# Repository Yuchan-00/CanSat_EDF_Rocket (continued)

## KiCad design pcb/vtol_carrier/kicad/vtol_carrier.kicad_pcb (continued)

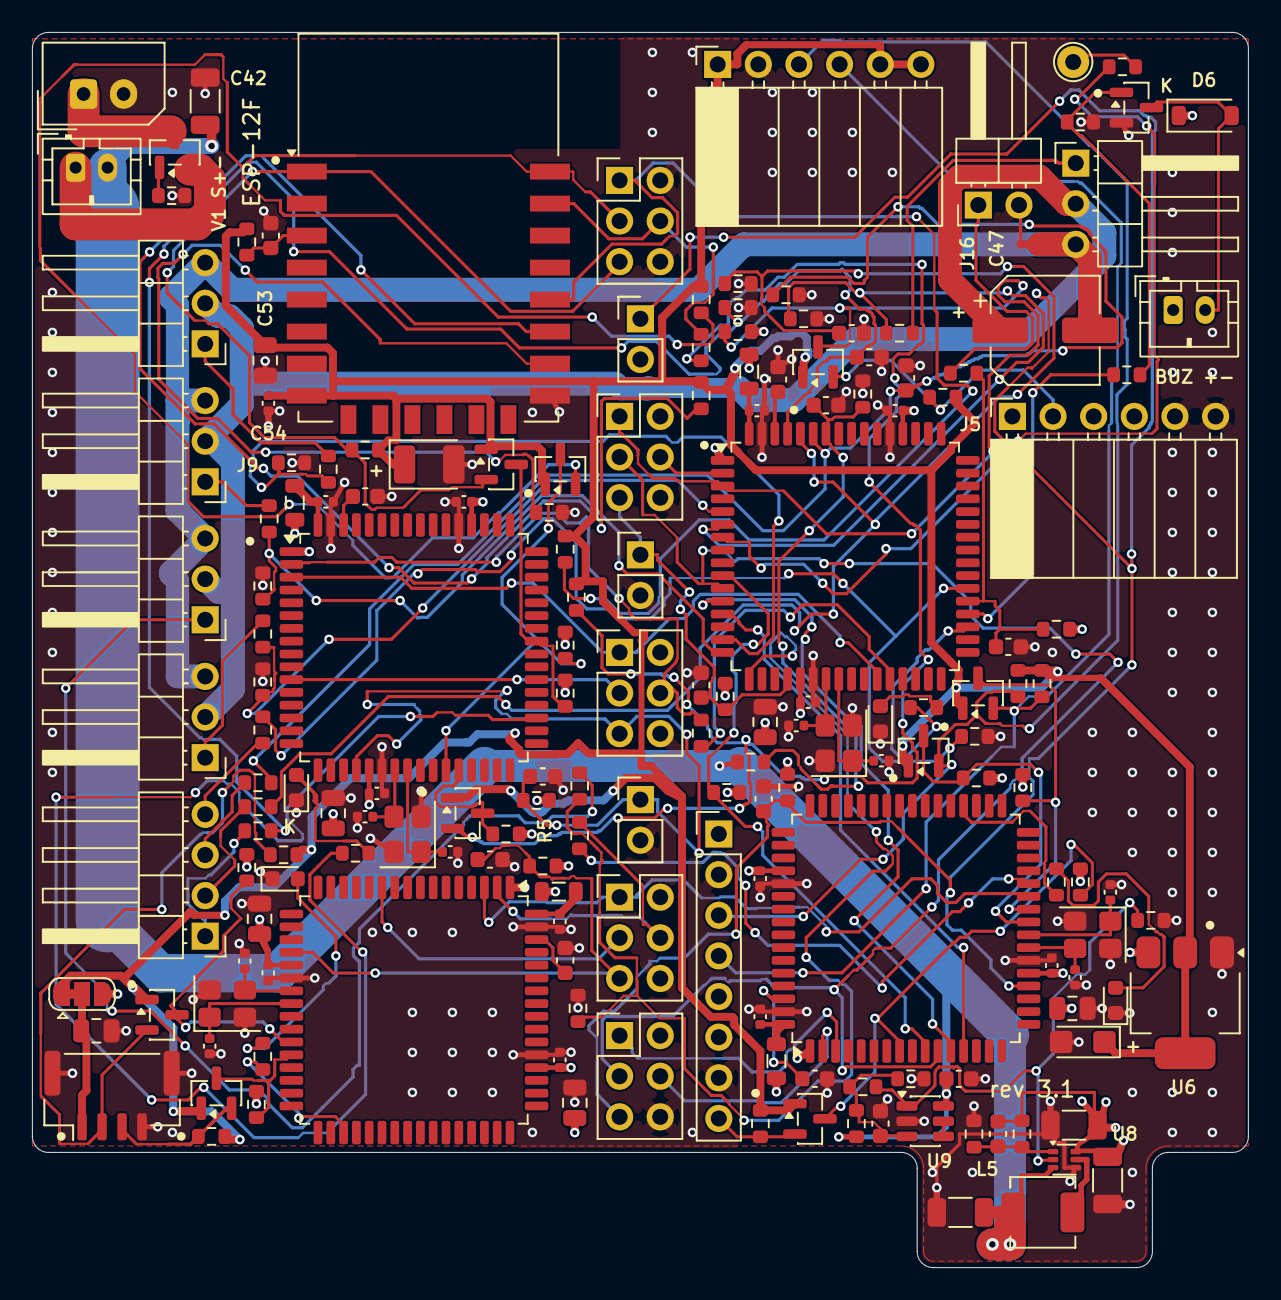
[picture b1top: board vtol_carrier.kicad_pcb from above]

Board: 4 copper layers, 76.0 x 77.2 mm, 176 parts (0 on the bottom side), 107 nets.

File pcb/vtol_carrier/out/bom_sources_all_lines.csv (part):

line,value,fitted refs,qty fitted,DNP refs,footprint,source,part number,MPN / name,JLC type,assembly,URL fetched,fetch date,stock at fetch
c100n0402,100n,C1 C2 C4 C9 C10 C12 C17 C18 C20 C25 C26 C28 C54,13,,Capacitor_SMD:C_0402_1005Metric,JLCPCB/LCSC,C1525,CL05B104KO5NNNC,Basic,JLC SMT assembly,https://jlcpcb.com/partdetail/C1525 https://cart.jlcpcb.com/shoppingCart/smtGood/getComponentDet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 https://www.lcsc.com/product-detail/multilayer-ceramic-capac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,2026-11-05,33539946
c10u0805,10u,C3 C11 C19 C27 C44 C53 C56,7,,Capacitor_SMD:C_0805_2012Metric,JLCPCB/LCSC,C15850,CL21A106KAYNNNE,Basic,JLC SMT assembly,https://jlcpcb.com/partdetail/C15850 https://cart.jlcpcb.com/shoppingCart/smtGood/getComponentDet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 https://www.lcsc.com/product-detail/multilayer-ceramic-capac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,2026-11-05,7647363
c100n0603,100n,C5 C8 C13 C16 C21 C24 C29 C32 C46 C48 C49 C50 C51 C55,14,,Capacitor_SMD:C_0603_1608Metric,JLCPCB/LCSC,C14663,CC0603KRX7R9BB104,Basic,JLC SMT assembly,https://jlcpcb.com/partdetail/C14663 https://cart.jlcpcb.com/shoppingCart/smtGood/getComponentDet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 https://www.lcsc.com/product-detail/multilayer-ceramic-capac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,2026-11-05,37483003
c27p0402,27p,C6 C7 C14 C15 C22 C23 C30 C31,8,,Capacitor_SMD:C_0402_1005Metric,JLCPCB/LCSC,C1557,0402CG270J500NT,Extended,JLC SMT assembly,https://jlcpcb.com/partdetail/C1557 https://cart.jlcpcb.com/shoppingCart/smtGood/getComponentDet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 https://www.lcsc.com/product-detail/multilayer-ceramic-capac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,2026-11-05,292832
c22u1206,22u 10V,C41 C42 C43,3,,Capacitor_SMD:C_1206_3216Metric,JLCPCB/LCSC,C12891,CL31A226KAHNNNE,Basic,JLC SMT assembly,https://jlcpcb.com/partdetail/C12891 https://cart.jlcpcb.com/shoppingCart/smtGood/getComponentDet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 https://www.lcsc.com/product-detail/multilayer-ceramic-capac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,2026-11-05,1628107
tant22u,22u 10V tantalum,C45,1,,Capacitor_Tantalum_SMD:CP_EIA-3216-18_Kemet-A,JLCPCB/LCSC,C7183,TAJA226M010RNJ,Extended,JLC SMT assembly,https://jlcpcb.com/partdetail/C7183 https://cart.jlcpcb.com/shoppingCart/smtGood/getComponentDet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 https://www.lcsc.com/product-detail/tantalum-capacitors_kyoc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,2026-11-05,2307
elec220u,220u 10V,C47,1,,Capacitor_SMD:CP_Elec_6.3x5.4,JLCPCB/LCSC,C2833309,RVT220UF10V67RV0037,Extended,JLC SMT assembly,https://jlcpcb.com/partdetail/C2833309 https://cart.jlcpcb.com/shoppingCart/smtGood/getComponentDet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 https://www.lcsc.com/product-detail/aluminum-electrolytic-ca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,2026-11-05,205404
tant100u,100u 10V tantalum,C52,1,,Capacitor_Tantalum_SMD:CP_EIA-3528-21_Kemet-B,JLCPCB/LCSC,C7196,TAJB107M010RNJ,Extended,JLC SMT assembly,https://jlcpcb.com/partdetail/C7196 https://cart.jlcpcb.com/shoppingCart/smtGood/getComponentDet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 https://www.lcsc.com/product-detail/tantalum-capacitors_kyoc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,2026-11-05,105178
led,LED 0603 (colour A),D1 D2 D3 D4,4,,LED_SMD:LED_0603_1608Metric,JLCPCB/LCSC,C2286,KT-0603R,Basic,JLC SMT assembly,https://jlcpcb.com/partdetail/C2286 https://cart.jlcpcb.com/shoppingCart/smtGood/getComponentDet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 https://www.lcsc.com/product-detail/led-indication-discrete_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,2026-11-05,6721348
schottky,SS14 / B5819W class Schottky,D6,1,,Diode_SMD:D_SOD-123,JLCPCB/LCSC,C8598,B5819W SL,Basic,JLC SMT assembly,https://jlcpcb.com/partdetail/C8598 https://cart.jlcpcb.com/shoppingCart/smtGood/getComponentDet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 https://www.lcsc.com/product-detail/schottky-diodes_jiangsu-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,2026-11-05,811852
gy521,1x8 2.54 mm (GY-521 soldered flat on straight pins),J1,1,,Connector_PinHeader_2.54mm:PinHeader_1x08_P2.54mm_Vertical,devicemart,no=1247052,MPU-6050 6축 자이로 가속도 센서 모듈 GY-521 [SZH-EK007],,hand-solder (devicemart module),https://www.devicemart.co.kr/goods/view?no=1247052 https://www.devicemart.co.kr/goods/search_sse_stream?search_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,2026-11-05,0
sock1x6ra,1x6 2.54 mm right-angle socket (module lies flat),J2 J5,2,,Connector_PinSocket_2.54mm:PinSocket_1x06_P2.54mm_Horizontal,JLCPCB/LCSC,C55629861,SH-PM254R-1x6P-H85,Extended,hand-solder (THT; JLC THT assembly optional),https://jlcpcb.com/partdetail/C55629861 https://cart.jlcpcb.com/shoppingCart/smtGood/getComponentDet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 ,2026-11-05,985
hdr2x3,2x3 2.54 mm vertical: ESP-12E programming header (3.3 V logic ONLY),,0,J3 J19 J20 J21 J22,Connector_PinHeader_2.54mm:PinHeader_2x03_P2.54mm_Vertical,JLCPCB/LCSC,C65114,2.54-2*3PPin,Extended,hand-solder (THT; JLC THT assembly optional),https://jlcpcb.com/partdetail/C65114 https://cart.jlcpcb.com/shoppingCart/smtGood/getComponentDet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 https://www.lcsc.com/product-detail/pin-headers_boomele-boom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,2026-11-05,41728
boost,"1x5 2.54 mm: Pololu S9V11F5S6CMA 5 V step-up/step-down module (VOUT, GND, VIN, EN, PG)",J6,1,,Connector_PinHeader_2.54mm:PinHeader_1x05_P2.54mm_Vertical,devicemart,no=15855364,5V Step-Up/Step-Down Voltage Regulator w/ Adjustable Low-Voltage Cutoff S9V11F5S6CMA #2870,,hand-solder (devicemart module),https://www.devicemart.co.kr/goods/view?no=15855364 https://www.devicemart.co.kr/goods/search_sse_stream?search_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,2026-11-05,100
gh4,JST-GH 1.25 mm 4-pin vertical (top entry),J7,1,,Connector_JST:JST_GH_BM04B-GHS-TBT_1x04-1MP_P1.25mm_Vertical,JLCPCB/LCSC,C161692,BM04B-GHS-TBT(LF)(SN),Extended,JLC SMT assembly,https://jlcpcb.com/partdetail/C161692 https://cart.jlcpcb.com/shoppingCart/smtGood/getComponentDet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 https://www.lcsc.com/product-detail/wire-to-board-connector_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,2026-11-05,23326
hdr1x3ra,"1x3 2.54 mm right-angle header (S, +, -)",J8 J9 J10 J11 J12,5,,Connector_PinHeader_2.54mm:PinHeader_1x03_P2.54mm_Horizontal,JLCPCB/LCSC,C55629817,SH-PZ254R-1x3P,Extended,hand-solder (THT; JLC THT assembly optional),https://jlcpcb.com/partdetail/C55629817 https://cart.jlcpcb.com/shoppingCart/smtGood/getComponentDet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 ,2026-11-05,2000
spox2,"Molex SPOX 5267-02A 2.50 mm 2-pin vertical (mates the pack's 5264-type housing, A)",J14,1,,Connector_Molex:Molex_SPOX_5267-02A_1x02_P2.50mm_Vertical,JLCPCB/LCSC,C5364642,22035025,Extended,hand-solder (THT; JLC THT assembly optional),https://jlcpcb.com/partdetail/C5364642 https://cart.jlcpcb.com/shoppingCart/smtGood/getComponentDet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 https://www.lcsc.com/product-detail/wire-to-board-connector_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,2026-11-05,454
ph2,JST-PH 2.0 2-pin vertical: lead to an external logic power switch,J15 J17,2,,Connector_JST:JST_PH_B2B-PH-K_1x02_P2.00mm_Vertical,JLCPCB/LCSC,C131337,B2B-PH-K-S(LF)(SN),Extended,hand-solder (THT; JLC THT assembly optional),https://jlcpcb.com/partdetail/C131337 https://cart.jlcpcb.com/shoppingCart/smtGood/getComponentDet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 https://www.lcsc.com/product-detail/wire-to-board-connector_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,2026-11-05,214800
hdr1x2ra,1x2 right-angle header,J16,1,,Connector_PinHeader_2.54mm:PinHeader_1x02_P2.54mm_Horizontal,JLCPCB/LCSC,C55629816,SH-PZ254R-1x2P,Extended,hand-solder (THT; JLC THT assembly optional),https://jlcpcb.com/partdetail/C55629816 https://cart.jlcpcb.com/shoppingCart/smtGood/getComponentDet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 ,2026-11-05,1750
hdr1x4ra,1x4 right-angle header,J18,1,,Connector_PinHeader_2.54mm:PinHeader_1x04_P2.54mm_Horizontal,JLCPCB/LCSC,C55629818,SH-PZ254R-1x4P,Extended,hand-solder (THT; JLC THT assembly optional),https://jlcpcb.com/partdetail/C55629818 https://cart.jlcpcb.com/shoppingCart/smtGood/getComponentDet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 ,2026-11-05,1898
hdr1x2v,2-pin header + shunt,,0,J24 J25 J26,Connector_PinHeader_2.54mm:PinHeader_1x02_P2.54mm_Vertical,JLCPCB/LCSC,C55629809,SH-PZ254V-1x2P,Extended,hand-solder (THT; JLC THT assembly optional),https://jlcpcb.com/partdetail/C55629809 https://cart.jlcpcb.com/shoppingCart/smtGood/getComponentDet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 ,2026-11-05,1662
ind10u,10uH,L1 L2 L3 L4,4,,Inductor_SMD:L_0805_2012Metric,JLCPCB/LCSC,C1046,SDFL2012S100KTF,Basic,JLC SMT assembly,https://jlcpcb.com/partdetail/C1046 https://cart.jlcpcb.com/shoppingCart/smtGood/getComponentDet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 https://www.lcsc.com/product-detail/inductors-smd_sunlord-sd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,2026-11-05,211090
bss138,BSS138,Q1 Q2 Q4 Q5 Q6 Q7 Q8 Q11,8,Q3,Package_TO_SOT_SMD:SOT-23,JLCPCB/LCSC,C40912,BSS138-7-F,Extended,JLC SMT assembly,https://jlcpcb.com/partdetail/C40912 https://cart.jlcpcb.com/shoppingCart/smtGood/getComponentDet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 https://www.lcsc.com/product-detail/mosfets_diodes-incorpora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,2026-11-05,409427
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
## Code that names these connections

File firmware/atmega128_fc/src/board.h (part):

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 * Every assignment below comes from params.json - FCU: flight_computer.pins, NAV: flight_computer.nav.pins,
 * COM: flight_computer.com.pins - through src/params_gen.h.  The generator checks each chip on its own against
 * the ATmega128 alternate-function table, refuses a pin used twice on the same chip, an ilink that is not on that
 * chip's USART and an nlink that is not on the SPI pins (PB0 = SS on both ends); this file only documents the pins
 * and turns the port letters into register names.  The same pin name on another chip is a different pin.
 *
 * ---- FCU (flight control unit: ilink on USART1, nlink SPI slave) ------------------------------------------------
 *  Signal              Pin        Function / level / notes
 *  ------------------  ---------  -------------------------------------------------------------
 *  vane 1 servo        PB5 OC1A   Timer1 fast PWM mode 14, 50 Hz, 5 V logic -> MG90S signal
 *  vane 2 servo        PB6 OC1B   Timer1
 *  vane 3 servo        PB7 OC1C   Timer1
 *  vane 4 servo        PE3 OC3A   Timer3 (same TOP / prescaler as Timer1)
 *  ESC throttle        PE4 OC3B   Timer3, 1000 us = off at boot and in every state except POWERED
 *  release servo       PE5 OC3C   Timer3, latched / released positions from fc_config.json
 *  nlink SS            PB0 SS     input with pull-up <- NAV PB0 (low during an exchange; an absent / resetting
 *                                 NAV leaves it high: the slave ignores SCK)
 *  nlink SCK           PB1 SCK    input <- NAV PB1.  PB1 is also the FCU's ISP SCK: hold the NAV in reset or
 *                                 unplug the nlink connector to program the FCU
 *  nlink MOSI          PB2 MOSI   input <- NAV PB2 (navigation frame)
 *  nlink MISO          PB3 MISO   output -> NAV PB3 (FCU state bytes)
 *  log out             PE1 TXD0   USART0 57600 8N1 -> OpenLog RXI.  PE0/PE1 are also the ISP
 *                                 PDI/PDO pins: unplug the OpenLog while programming the FCU
 *  battery voltage     PF0 ADC0   divider, internal 2.56 V reference (100 nF on AREF)
 *  status LED          PC0        active high, 1k resistor
 *  buzzer              PC1        active high into an NPN driver (5 V active buzzer)
 *  arm switch          PC2        to GND when armed, internal pull-up
 *  ilink RX            PD2 RXD1   <- COM PE1 TXD0, direct (ILINK_BAUD 8N1)
 *  ilink TX            PD3 TXD1   -> 1 kOhm series resistor -> COM PE0 RXD0
 *  ISP                 PE0/PE1/PB1/RESET  PDI / PDO / SCK - NOT PB2/PB3 on the ATmega128
 *  (v0.6.3: no I2C, no sensor on the FCU - PD0/PD1/PE6 are free)
 *
 * ---- NAV (navigation computer: sensors on TWI, nlink SPI master) ------------------------------------------------
 *  I2C SCL / SDA       PD0 / PD1  TWI 400 kHz, 5 V side of the BSS138 shifter; 3.3 V side to
 *                                 GY-521 (MPU-6050 0x68) and the barometer module (BMP280 TYE-BMP29 0x77;
 *                                 the GY-63 MS5611 of the build option also 0x77)
 *  MPU INT (optional)  PE6 INT6   not used by the baseline firmware (polled at the 250 Hz tick)
 *  nlink SS            PB0        output, high = idle (made an output BEFORE the SPI is enabled as master)
 *  nlink SCK           PB1 SCK    output -> FCU PB1 (also the NAV's own ISP SCK)
 *  nlink MOSI          PB2 MOSI   output -> FCU PB2
 *  nlink MISO          PB3 MISO   input with pull-up <- FCU PB3 (0xFF when no FCU answers)
 *  status LED          PC1        active high, 1k resistor (NAV_LED_* below)
 *  ISP                 PE0/PE1/PB1/RESET  while the NAV is held in reset its PB0-PB2 float: the FCU's SS
 *                                 pull-up keeps the FCU's SPI idle while the programmer clocks PB1
 *
 * ---- COM (radio link processor: ESP-12E bridge by default, LoRa fallback; ilink on USART0) -----------------------------------------------------------------
 *  ilink RX            PE0 RXD0   <- 1 kOhm <- FCU PD3 TXD1.  PE0 is also the COM's ISP PDI:
 *                                 unplug the ilink connector to program the COM (left plugged by
 *                                 mistake, the resistor caps the FCU-vs-programmer current at 5 mA)
 *  ilink TX            PE1 TXD0   -> FCU PD2 RXD1, direct.  Also the COM's ISP PDO
 *  status LED          PC0        active high, 1k resistor (COM_LED_* below)
 *  --- LoRa ground link (SPEC 10.3), backend lora_uart (Ebyte transparent module) ---
 *  link RX             PD2 RXD1   <- module TXD, direct
 *  link TX             PD3 TXD1   -> module RXD through a BSS138 channel
 *  M0 / M1             PC3 / PC4  -> module through BSS138 channels, driven low = normal mode
 *  AUX                 PC5        <- module, direct, input with pull-up
 *  --- backend sx127x (SX1276/77/78 on SPI) ---
 *  NSS / SCK / MOSI    PB0/PB1/PB2 -> module through BSS138 channels (NSS is the SPI SS pin: an
 *                                 output, so the SPI stays master)
 *  MISO                PB3        <- module, direct
 *  DIO0                PE7        <- module, direct (polled)
 *  RESET               PC6        -> module through a BSS138 channel
 *  ISP                 PE0/PE1/PB1/RESET  PB1 is also the radio SCK: the shifter pull-up keeps
 *                                 NSS high while the COM is held in reset for programming
 *
 * ---- nlink wiring (flight_computer.nlink: SPI mode 0, NLINK_SPI_HZ, NLINK_BYTE_GAP_US; SPEC 10.5) --------------
 *   NAV PB0 SS   ------------> FCU PB0 SS      (FCU pull-up: idle high)
 *   NAV PB1 SCK  ------------> FCU PB1 SCK     (FCU ISP SCK: hold the NAV in reset or unplug the nlink
 *                                               connector to program the FCU)
 *   NAV PB2 MOSI ------------> FCU PB2 MOSI
 *   NAV PB3 MISO <------------ FCU PB3 MISO    (NAV pull-up)
 *   GND -------------------- GND               (common ground; both 5 V parts on the 5 V logic UBEC, no shifter)
 *   A dead NAV or a cut wire: no valid frame, the FCU's tick runs on its frame timeout with imu_ok = baro_ok =
 *   false -> I9 after the supervisor's IMU failure time (SPEC 10.5).
 *
 * ---- ilink wiring (flight_computer.ilink: ILINK_BAUD 8N1, U2X = 0) ----------------------------------------------
 *   FCU PD3 TXD1 --[1 kOhm]--> COM PE0 RXD0      (series_resistor_ohm; COM ISP PDI)
 *   FCU PD2 RXD1 <------------ COM PE1 TXD0      (COM ISP PDO)
 *   GND -------------------- GND                (common ground)
 *   Both chips are 5 V parts on the 5 V logic UBEC: no level shifter on the ilink.
 *   A dead COM or a broken wire is a lost radio link for the FCU's supervisor (I1p / I1).
 *
 * ---- v0.8.1: GNS (the fourth ATmega128A: GPS receiver, UBX, GPS filter, position controller; -D FC_ROLE_GNS) ------
 * (params flight_computer.gns.pins, electronics.gns, electronics.gps; src/gns/gns_main.c)
 *  GPS RX              PD2 RXD1   <- GPS receiver TX (NEO-7M; NEO-6M in v0.8) through the GNS's BSS138 channel (GPS_BAUD 8N1 after the boot config)
 *  GPS TX              PD3 TXD1   -> BSS138 -> GPS receiver RX (3.3 V side: the receiver's RX is not 5 V tolerant)
 *  glink RX            PE0 RXD0   <- NAV PD3 TXD1 (GLINK_BAUD 8N1).  PE0 is the GNS's ISP PDI
 *  glink TX            PE1 TXD0   -> NAV PD2 RXD1.  PE1 is the GNS's ISP PDO: unplug the glink to program the GNS
 *  status LED          PC0        active high, 1k resistor (GNS_LED_* below)
 *  (the NAV's USART1 PD2 / PD3 is the glink since v0.8.1 - the GPS lead goes to the GNS)
 *
 * ---- glink wiring (flight_computer.glink: GLINK_BAUD 8N1, U2X = 0; core/glink_proto.h) ----------------------------
 *   NAV PD3 TXD1 ------------> GNS PE0 RXD0     (GNS ISP PDI)
 *   NAV PD2 RXD1 <------------ GNS PE1 TXD0     (GNS ISP PDO)
 *   GND -------------------- GND                (common ground; both 5 V parts on the 5 V logic UBEC, no shifter)
 *   A dead GNS or a cut wire: no RESULT frames, the NAV sends SLOT_EMPTY, the FCU falls back to the TRIM after 2 cycles
 *   and raises its own GPS_LOST (V11 LAND) after land_steps cycles (core/nlink_proto.h nl_gns_rx).
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#define ARM_SW_PINR FC_CAT(PIN, PIN_ARM_SW_PORT)

/* NAV */
#define NAV_LED_PORT     FC_CAT(PORT, PIN_NAV_LED_PORT)
#define NAV_LED_DDR      FC_CAT(DDR, PIN_NAV_LED_PORT)
#define NAV_LED_PINR     FC_CAT(PIN, PIN_NAV_LED_PORT)

/* GNS (v0.8.1): params flight_computer.gns.pins.led = "PC0"; tools/gen_firmware_params.py emits no PIN_GNS_LED_* yet, so
 * the pin is taken from that params entry here (the generator's pin check does not cover the GNS - a request) */
#ifndef PIN_GNS_LED_PORT
#define PIN_GNS_LED_PORT C
#define PIN_GNS_LED_BIT  0
#endif
#define GNS_LED_PORT     FC_CAT(PORT, PIN_GNS_LED_PORT)
#define GNS_LED_DDR      FC_CAT(DDR, PIN_GNS_LED_PORT)

/* COM */
#define COM_LED_PORT     FC_CAT(PORT, PIN_COM_LED_PORT)
#define COM_LED_DDR      FC_CAT(DDR, PIN_COM_LED_PORT)
#define COM_LED_PINR     FC_CAT(PIN, PIN_COM_LED_PORT)

#define LINK_M0_PORTR    FC_CAT(PORT, PIN_LINK_M0_PORT)
#define LINK_M0_DDR      FC_CAT(DDR, PIN_LINK_M0_PORT)
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
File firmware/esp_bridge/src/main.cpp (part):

/* ESP8266 UART <-> ESP-NOW bridge (README.md): ONE sketch for both ends of the vehicle link.
 *
 *   -D BRIDGE_ROLE_VEHICLE  the ESP-12E soldered on the VTOL carrier (U7) or wired to the rocket's COM board: UART0
 *                           (GPIO1 TXD0 / GPIO3 RXD0) <-> the COM's USART1 through BSS138 channels; the COM holds it in
 *                           reset at a cold COM boot and releases it (COM PC6 -> RST, open-drain, hal/esp_bridge.c); a
 *                           COM-only reset leaves it running
 *   -D BRIDGE_ROLE_GROUND   an ESP-07S-class module (u.FL, external 8-14 dBi antenna) on a 3.3 V USB-UART: UART0 <-> the
 *                           PC (tools/ground_station.py --link-hw esp_bridge)
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 * BRIDGE_SEND_TIMEOUT_US without one (A: the SDK's callback timing is not measured).  The link protocol is half-duplex
 * polling (one request, one reply, 2 Hz), so a packet rarely waits.
 *
 * Diagnostics (review LB-4): -D BRIDGE_DEBUG_UART1 prints the counters once per second on Serial1 (GPIO2, UART1 TX only,
 * 115200 8N1) - for the range test with a 3.3 V USB-UART on GPIO2; GPIO2 already has its 10 k boot pull-up and UART1
 * idles high, so the boot strap is kept (A; the ESP-12E's on-module LED may sit on GPIO2 and blink, A).  Off by default:
 * the link UART (UART0) never carries anything but link bytes.
 */
#include <Arduino.h>
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    esp_now_register_recv_cb(on_recv);
    esp_now_register_send_cb(on_sent);
#ifdef BRIDGE_DEBUG_UART1
    Serial1.begin(115200, SERIAL_8N1);            /* GPIO2, TX only */
#endif
}

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                               (unsigned long)s_send_dropped, (unsigned long)s_send_timeouts,
                               (unsigned long)s_rx_packets, (unsigned long)s_rx_foreign,
                               (unsigned long)s_down.dropped_packets(), (unsigned long)s_down.dropped_bytes()};
    for (unsigned i = 0; i < sizeof v / sizeof v[0]; i++) {   /* UART1 only (GPIO2); UART0 stays link bytes */
        Serial1.print(names[i]);
        Serial1.print(v[i]);
    }
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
